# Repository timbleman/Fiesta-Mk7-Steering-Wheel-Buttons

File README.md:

# Fiesta-Mk7-Steering-Wheel-Buttons

## Introduction
My Ford Fiesta has media buttons on its steering wheel, but these have no function when using the AUX audio input.
This code adds functionality to these buttons of a mk7 Ford 
Fiesta with the audio package 1. With the correspondent hardware songs 
can be skipped and paused via the AUX cord. Long pressing the prev button
launches the google assistant on android phones. 

## Usage and requirements
An ATtiny45 Microcontroller is used to read inputs from the buttons.
The headset button shorts the function and ground terminal of the AUX cable.
Wiring diagrams and a PCB-design (designed in KiCad) are in the repository.
The directory pics/ includes images that explain which wires in the steering console are tapped.
The electronics are stored beneath the center console at the gear lever.
It is recommended to wrap the electronics in some foam, to damped the clicking of the relay.
The code is entirely low level and does not rely on the Arduino libraries.

## Future work
A sleep mode may be added, but isn't necessary depending on the power
source and due to the low energy consumption of the ATtiny45.
Settings may need to be tweaked.

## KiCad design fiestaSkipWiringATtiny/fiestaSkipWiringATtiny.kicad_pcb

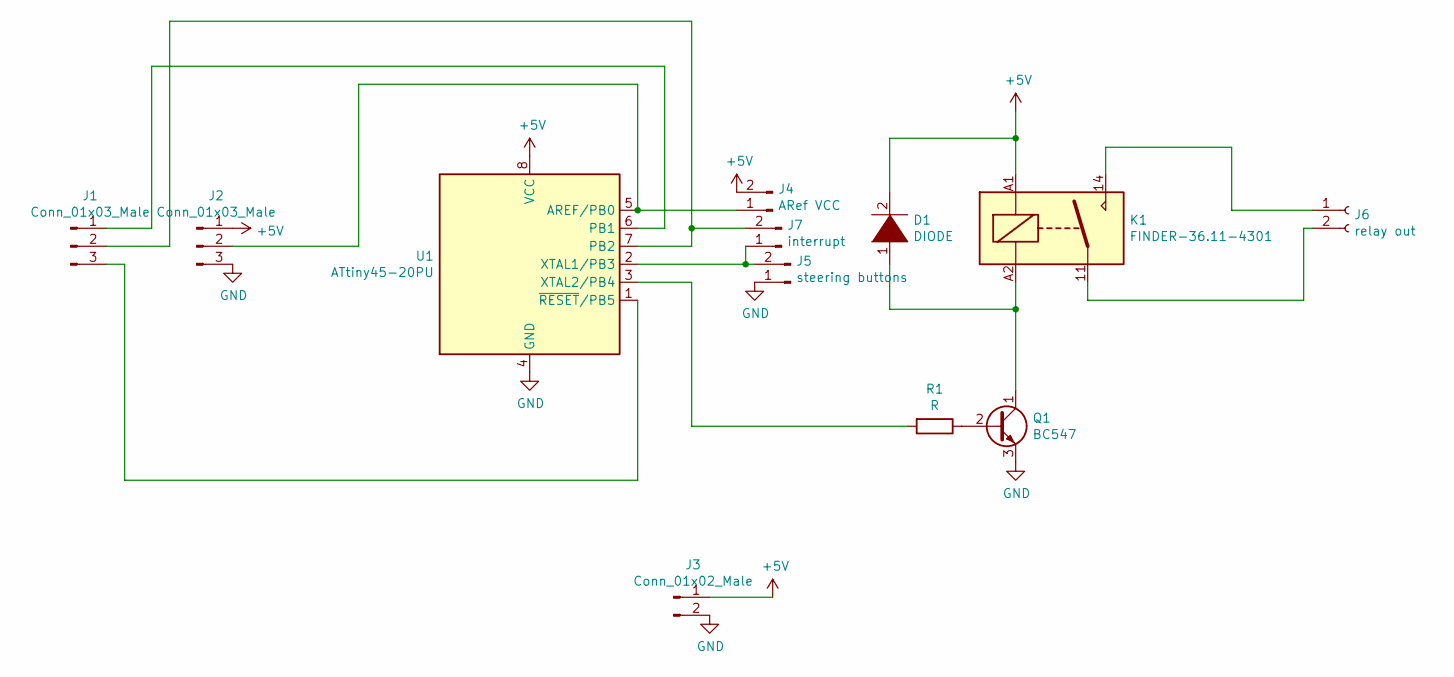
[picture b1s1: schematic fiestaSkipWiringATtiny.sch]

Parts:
D1: DIODE; D_DO-41_SOD81_P10.16mm_Horizontal
J1, J2: Conn_01x03_Male; PinSocket_1x03_P2.54mm_Vertical
J3: Conn_01x02_Male; PinSocket_1x02_P2.54mm_Vertical
J4: ARef VCC; PinSocket_1x02_P2.54mm_Vertical
J5: steering buttons; PinSocket_1x02_P2.54mm_Vertical
J6: relay out; PinSocket_1x02_P2.54mm_Vertical
J7: interrupt; PinSocket_1x02_P2.54mm_Vertical
K1: FINDER-36.11-4301; Relay_SPDT_Finder_36.11
Q1: BC547; TO-92_Inline
R1: R; R_Axial_DIN0207_L6.3mm_D2.5mm_P10.16mm_Horizontal
U1: ATtiny45-20PU; DIP-8_W7.62mm

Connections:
+5V: D1.2 (A), J2.1, J3.1, J4.2, K1.A1, U1.8 (VCC)
GND: J2.3, J3.2, J5.1, Q1.3 (E), U1.4 (GND)
unnamed: D1.1 (K), K1.A2, Q1.1 (C)
unnamed: J1.1, U1.6 (PB1)
unnamed: J1.2, J7.2, U1.7 (PB2)
unnamed: J1.3, U1.1 (~RESET~/PB5)
unnamed: J2.2, J4.1, U1.5 (AREF/PB0)
unnamed: J5.2, J7.1, U1.2 (XTAL1/PB3)
unnamed: J6.1, K1.14
unnamed: J6.2, K1.11
unnamed: Q1.2 (B), R1.1
unnamed: R1.2, U1.3 (XTAL2/PB4)

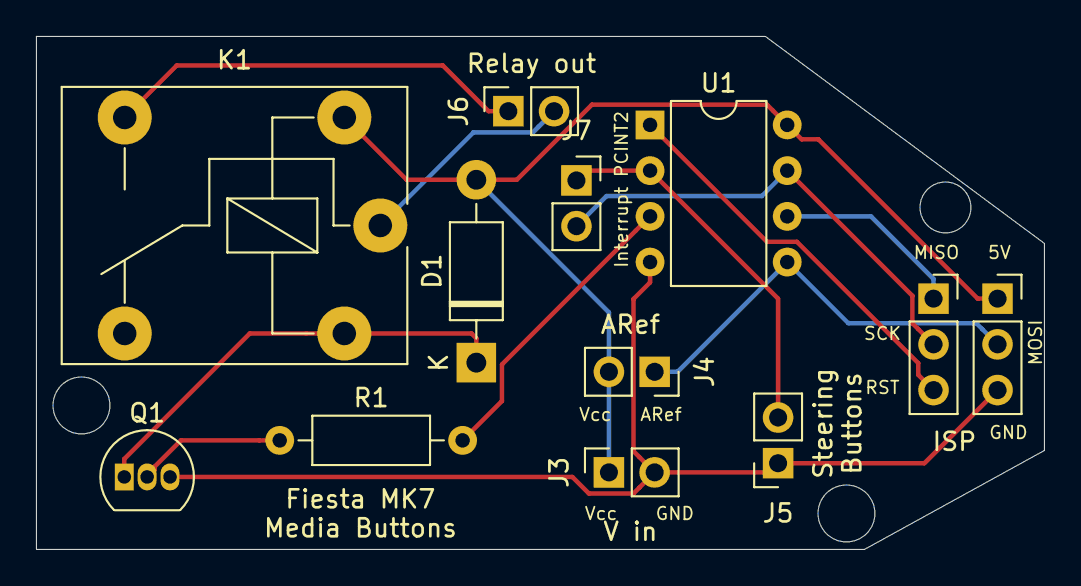
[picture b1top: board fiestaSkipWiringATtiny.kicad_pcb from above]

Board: 2 copper layers, 56.0 x 28.5 mm, 12 parts (0 on the bottom side), 12 nets.

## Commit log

2019-08-12 added Atmega328p code
2019-08-12 changed pins, adjusted analog read
2019-08-12 added google assistant start
2019-08-12 added comments
2019-08-12 added pics and wiring
2021-02-14 made google assistant launch quicker
2021-02-14 updated pics and readme
